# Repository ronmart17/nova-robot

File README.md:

# NOVA — a small desktop robot with a Raspberry Pi 5 brain

NOVA is a palm-sized home robot designed end to end: electronics, PCBs, enclosure, charging dock, simulations and
documentation. A Raspberry Pi 5 does vision, voice and the link to cloud AI models. An ESP32-S3 keeps the body alive:
motors, sensors, display face and power. The robot drives back to a 12 V dock by itself to charge.

> **Status:** Rev B design complete and verified (ERC/DRC clean, mechanical interference check, circuit and system
> simulations). The physical prototype has not been built yet.

| | |
|---|---|
|  |  |
| On its charging dock (AprilTag for the return trip) | Five-part enclosure: white body, graphite skirt, smoked visor, light halo |
|  |  |
| Internals: main board, 2S2P pack, Pi 5, XVF3800 mic array, head board | Rear: speaker grille, USB-C, power switch, dock opening |

## What is inside

| Block | Parts |
|---|---|
| Brain | Raspberry Pi 5 + Active Cooler, Camera Module 3, ReSpeaker XVF3800 4-mic array with echo cancellation |
| Body controller | ESP32-S3-WROOM-1 (N16R8), TCA9535 I/O expander, LSM6DSOX IMU |
| Drive | 2 × N20 gear motors with Hall encoders, TB6612FNG, ball caster |
| Sensors | 2 × VL53L4CD cliff ToF, VL53L1X front ToF, AT42QT1010 capacitive touch |
| Face | 2.0" ST7789 IPS display behind a smoked acrylic visor |
| Power | 2S2P 18650 (44 Wh), R5460 protector, TI BQ25798 buck-boost NVDC charger with two inputs (USB-C and 12 V dock), TPS566238 6 A for the Pi 5, TPS62933 for 3.3 V |
| Dock | 12 V input with PTC, reverse-polarity FET and TVS, spring pogo contacts, AprilTag target |
| Pi ↔ ESP32 | UART0 (the Pi can re-flash the ESP32 through its ROM bootloader), shutdown/reset/boot lines |

Cloud AI: the hardware is laid out so that the Pi 5 runs the voice pipeline (wake word and audio from the XVF3800)
and calls hosted LLM, speech and vision APIs over Wi-Fi, while light models (wake word, AprilTag, small vision models)
run on the device. The firmware and software are the next step.

## Boards (KiCad 10)

| Board | Layers | Size | Verification |
|---|---|---|---|
| `nova-main` | 4 | 136 × 136 mm | ERC 0 (3 documented exclusions), DRC 0, 0 unconnected, schematic parity 0 |
| `nova-head` | 2 | 76 × 74.9 mm | ERC 0, DRC 0, 0 unconnected, parity 0 |
| `nova-dock` | 2 | 58 × 34 mm + break-away contact plate | ERC 0, DRC 0, 0 unconnected, parity 0 |

| | | |
|---|---|---|
|  |  |  |
| Main board | Head board | Dock board |

Each board has JLCPCB-ready Gerbers, BOM and CPL files, a full BOM with Mouser/DigiKey codes, assembly drawings,
a 1:1 mechanical drawing and STEP in `hardware/<board>/fabrication/`.

## Simulations

Circuit simulations in ngspice and system analyses in Python. Full report:
[simulations/NOVA_RevB_simulations.pdf](simulations/NOVA_RevB_simulations.pdf).

| Check | Result |
|---|---|
| Pi 5 rail, 1 → 3 A load step (behavioural D-CAP3 model) | ≥ 4.90 V at the Pi (under-voltage at 4.63 V), 3.9 mV ripple |
| VSYS with both motors under PWM | 46 mV p-p driving, 108 mV p-p with both motors stalled |
| Dock and USB-C hot plug, reverse polarity | ≤ 19.5 V at the charger input (30 V max), reversed adapter blocked |
| I2C and display SPI edges | 207 ns rise time (≤ 300 ns), SPI ringing removed with a lower drive strength |
| Runtime (44 Wh) | 10 h idle, 6.9 h in conversation, 4.3 h at full load, 11 days standby |
| Docking (Monte Carlo) | 99 % first-try success with the recommended approach procedure |
| Stability, thermal, pogo-contact current, battery protection | see the report |

## Repository layout

```
docs/          design document (MD + PDF), images, verification summary
hardware/      KiCad 10 projects: nova-main, nova-head, nova-dock, project library (lib/), fabrication outputs
mechanics/     CadQuery enclosure and assembly (Python), renders, printed parts (STEP + STL), assembly STEP
generator/     Python generators for the schematics, footprints, PCB placement/routing and the documentation
simulations/   ngspice and Python models, netlists, plots, results and the simulation report
```

The schematics and boards are generated by the scripts in `generator/` (including an in-house PathFinder-style
router); the enclosure is parametric CadQuery code driven by `mechanics/dims.py`. The scripts were written for the
author's build environment (KiCad 10.0.7 built from source, absolute paths), so treat them as reference.

## Tools

KiCad 10 · ngspice 42 · CadQuery / OpenCascade · Python (numpy, matplotlib, pyvista)

## Author and licence

Designed by **Caril Ronnie Martínez Vera** — electronics and telecommunications engineer.
© 2026, all rights reserved: see [LICENSE](LICENSE). The files are published for viewing only.

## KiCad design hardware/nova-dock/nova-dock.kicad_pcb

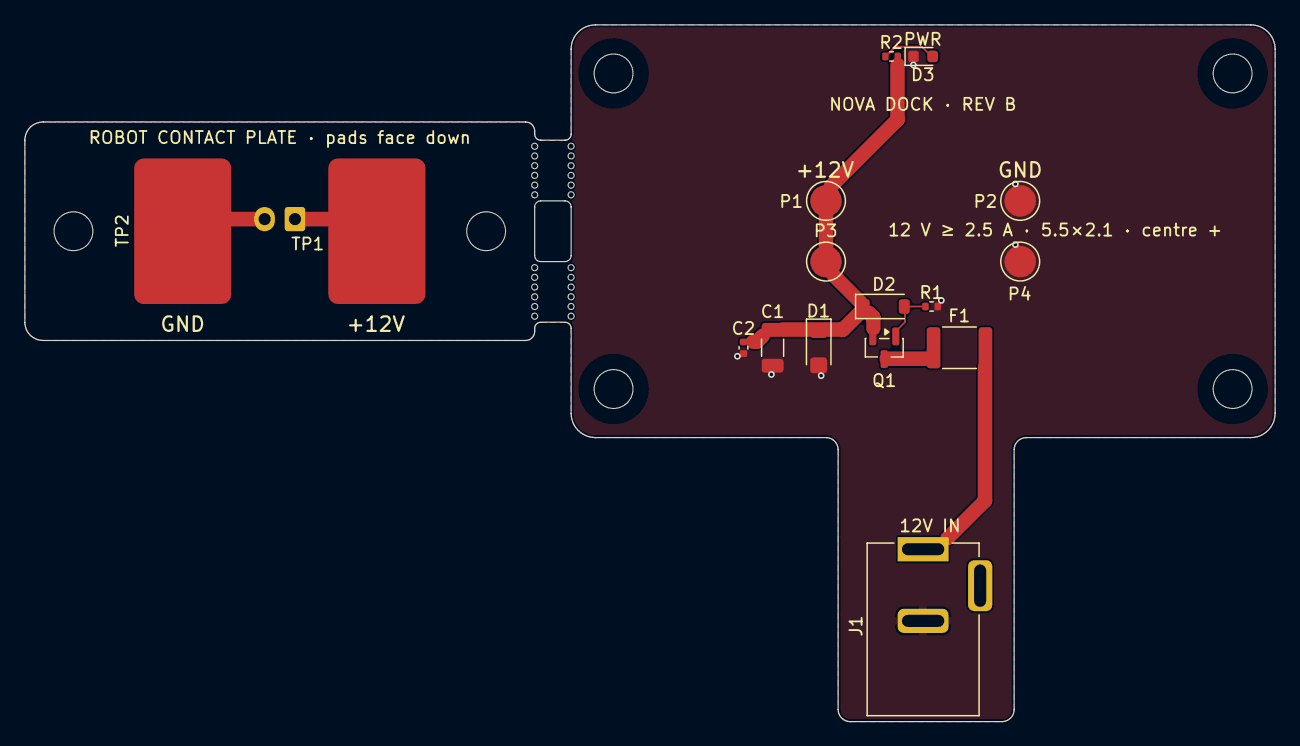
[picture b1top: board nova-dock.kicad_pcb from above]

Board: 2 copper layers, 103.0 x 57.4 mm, 25 parts (1 on the bottom side), 8 nets.

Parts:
C1: 22u/25V; C_1206_3216Metric
C2: 100n; C_0402_1005Metric
D1: SMF15A; D_SMF
D2: BZT52C10; D_SOD-123
D3: Green; LED_0603_1608Metric
F1: 3A hold; Fuse_1812_4532Metric
H1, H2, H3, H4, H5, H6: M3; MountingHole_3.2mm_M3
J1: 12V IN; DC_Jack_XKB_DC-005-5A-2.0_Horizontal
J2: TO ROBOT; JST_XH_B2B-XH-A_1x02_P2.50mm_Vertical
MB1, MB2: TAB; MouseBite_Tab_5x3mm
P1, P2, P3, P4: POGO; Pogo_YTC1P-8020_D2.0mm
Q1: AO3401A; SOT-23
R1: 10k; R_0402_1005Metric
R2: 4.7k; R_0402_1005Metric
TP1, TP2: CONTACT; ContactPad_8x12mm

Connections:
/PLATE_GND: J2.2, TP2.1 (1_1)
/PLATE_POS: J2.1, TP1.1 (1_1)
/VDOCK_OUT: C1.1, C2.1, D1.1 (A1), D2.1 (K), P1.1 (Pin_1_1), P3.1 (Pin_1_1), Q1.2 (S), R2.1
GND: C1.2, C2.2, D1.2 (A2), D3.1 (K), J1.2, P2.1 (Pin_1_1), P4.1 (Pin_1_1), R1.2
unnamed: D2.2 (A), Q1.1 (G), R1.1
unnamed: D3.2 (A), R2.2
unnamed: F1.1, J1.1
unnamed: F1.2, Q1.3 (D)

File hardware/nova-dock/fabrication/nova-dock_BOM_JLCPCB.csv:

Comment,Designator,Footprint,JLCPCB Part #
22u/25V,C1,C_1206_3216Metric,C12891
100n,C2,C_0402_1005Metric,C307331
SMF15A,D1,D_SMF,C123802
BZT52C10,D2,D_SOD-123,C173431
Green,D3,LED_0603_1608Metric,C125098
3A hold,F1,Fuse_1812_4532Metric,C883162
12V IN,J1,DC_Jack_XKB_DC-005-5A-2.0_Horizontal,C381116
TO ROBOT,J2,JST_XH_B2B-XH-A_1x02_P2.50mm_Vertical,C158012
POGO,"P1,P2,P3,P4",Pogo_YTC1P-8020_D2.0mm,C5221286
AO3401A,Q1,SOT-23,C15127
10k,R1,R_0402_1005Metric,C60490
4.7k,R2,R_0402_1005Metric,C105871

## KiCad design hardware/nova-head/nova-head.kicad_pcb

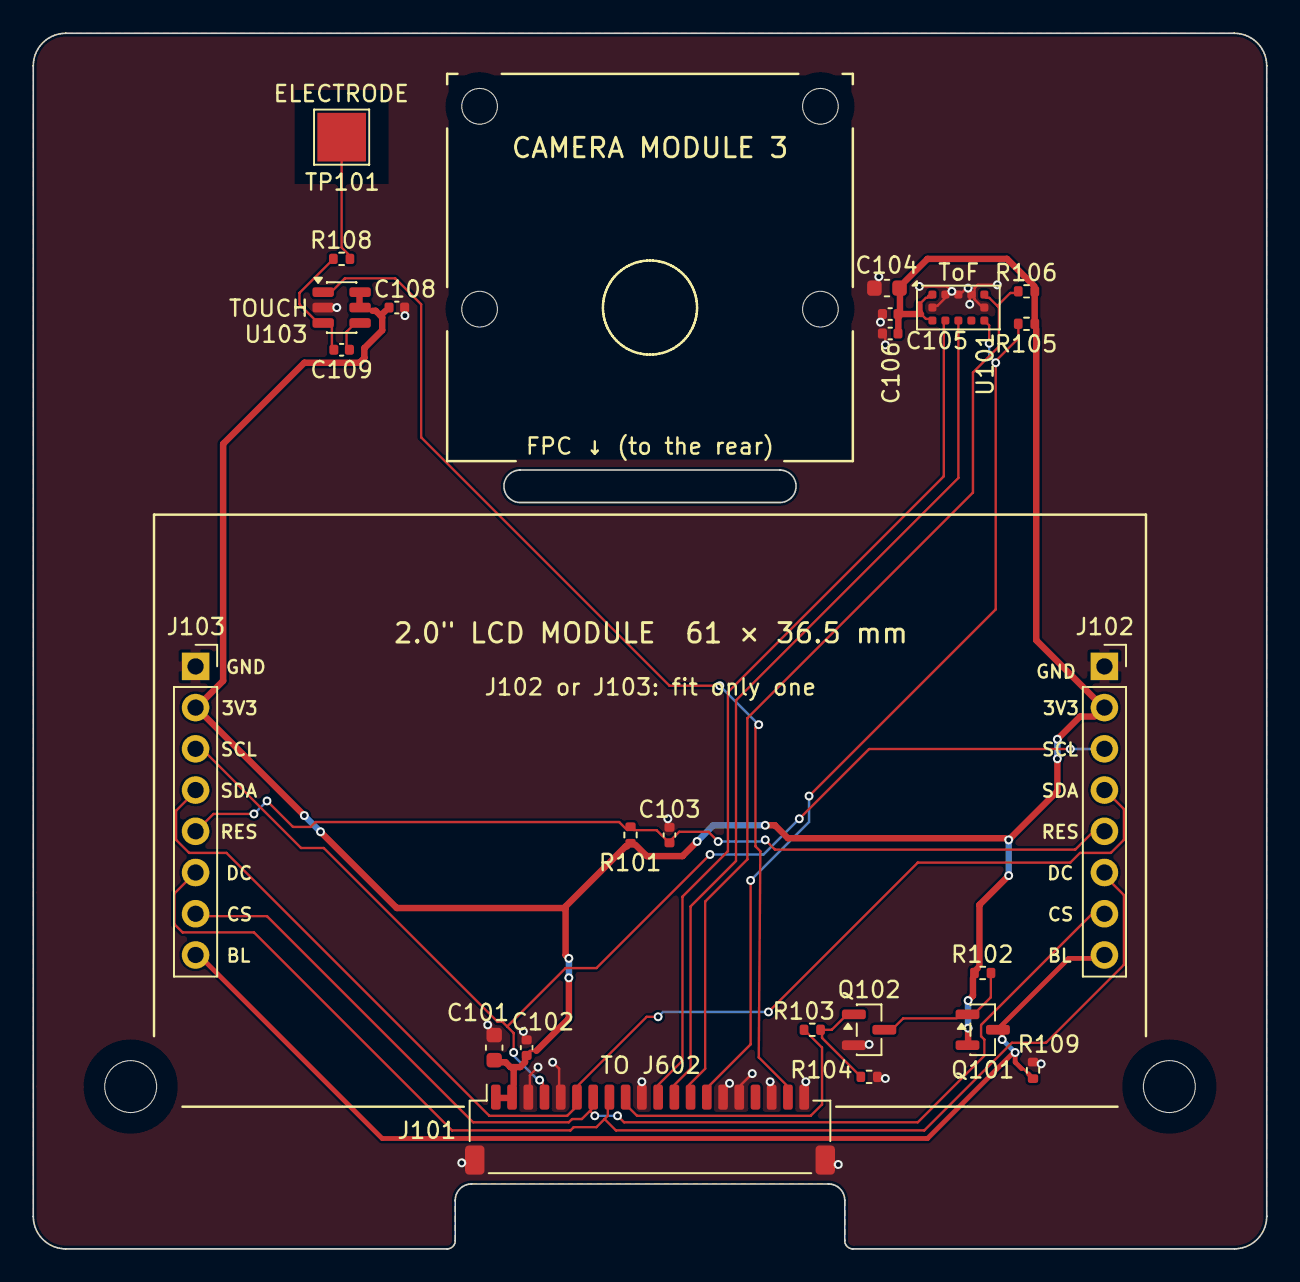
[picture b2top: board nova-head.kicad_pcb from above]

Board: 2 copper layers, 76.0 x 74.9 mm, 30 parts (0 on the bottom side), 19 nets.

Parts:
C101: 10u/10V; C_0603_1608Metric
C102, C103, C105, C106, C108: 100n; C_0402_1005Metric
C104: 4.7u/16V; C_0603_1608Metric
C109: 8.2n; C_0402_1005Metric
H101, H102: M3; MountingHole_3.2mm_M3
H103, H104, H105, H106: M2; MountingHole_2.2mm_M2
J101: HEAD; JST_SH_SM20B-SRSS-TB_1x20-1MP_P1.00mm_Horizontal
J102, J103: LCD ST7789; PinSocket_1x08_P2.54mm_Vertical
Q101: AO3401A; SOT-23
Q102: 2N7002LT1G; SOT-23
R101, R102, R105, R106: 10k; R_0402_1005Metric
R103: 100R; R_0402_1005Metric
R104: 100k; R_0402_1005Metric
R108: 4.7k; R_0402_1005Metric
R109: 1k; R_0402_1005Metric
TP101: TOUCH; TestPoint_Pad_3.0x3.0mm
U101: VL53L1CXV0FY/1; ST_VL53L1x
U103: AT42QT1010-TSHR; SOT-23-6

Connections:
+3V3: C101.1, C102.1, C104.1, C105.1, C106.1, C108.1, J101.1, J101.2, J102.2, J103.2, Q101.2 (S), R101.1, R102.1, R105.1, R106.1, U101.1 (AVDDVCSEL), U101.11 (AVDD), U103.5 (VDD), U103.6 (SYNC)
/BL_OUT: J102.8, J103.8, Q101.3 (D), R109.1
/I2C_SCL: J101.11, U101.10 (SCL)
/I2C_SDA: J101.12, U101.9 (SDA)
/LCD_BL: J101.9, R103.1
/LCD_CS: J101.7, J102.7, J103.7
/LCD_DC: J101.8, J102.6, J103.6
/LCD_MOSI: J101.6, J102.4, J103.4
/LCD_RES: C103.1, J102.5, J103.5, R101.2
/LCD_SCLK: J101.4, J102.3, J103.3
/TOF_INT: J101.14, R105.2, U101.7 (GPIO1)
/TOF_XSHUT: J101.13, R106.2, U101.5 (XSHUT)
/TOUCH: J101.19, U103.1 (OUT)
GND: C101.2, C102.2, C103.2, C104.2, C105.2, C106.2, C108.2, J101.3, J101.5, J101.10, J101.15, J101.16, J101.18, J101.20, J101.MP (MountPin), J102.1, J103.1, Q102.2 (S), R104.2, R109.2, U101.2 (AVSSVCSEL), U101.3 (GND), U101.4 (GND), U101.6 (GND), U101.12 (GND), U103.2 (VSS)
unnamed: Q101.1 (G), Q102.3 (D), R102.2
unnamed: Q102.1 (G), R103.2, R104.1
unnamed: R108.2, TP101.1 (1_1)
unnamed: C109.2, U103.4 (SNS)
unnamed: C109.1, R108.1, U103.3 (SNSK)

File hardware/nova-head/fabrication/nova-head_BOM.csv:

Item,Qty,Designators,Value,Footprint,Manufacturer,MPN,LCSC,Mouser,DigiKey,Alt MPN,Alt Mouser,Alt DigiKey,Description,Sourcing note,DNP
1,1,C101,10u/10V,C_0603_1608Metric,Yageo,CC0603KRX5R6BB106,C326057,603-CC603KRX5R6BB106,,,,,MLCC 10uF 10V X5R 0603,JLC Basic alt C19702,
2,5,"C102, C103, C105, C106, C108",100n,C_0402_1005Metric,Samsung,CL05B104KB54PNC,C307331,187-CL05B104KB54PNC,1276-CL05B104KB54PNCCT-ND,,,,MLCC 100nF 50V X7R 0402,JLC Basic,
3,1,C104,4.7u/16V,C_0603_1608Metric,Samsung,CL10A475KO8NNNC,C19666,,1276-1784-1-ND,,,,MLCC 4.7uF 16V X5R 0603,JLC Basic,
4,1,C109,8.2n,C_0402_1005Metric,Yageo,CC0402KRX7R9BB822,C107032,603-CC402KRX7R9BB822,311-3817-1-ND,,,,MLCC 8.2nF 50V X7R 0402 — QT1010 Cs,,
5,1,J101,HEAD,JST_SH_SM20B-SRSS-TB_1x20-1MP_P1.00mm_Horizontal,JST,SM20B-SRSS-TB(LF)(SN),C160415,306-SM20BSRSSTBLFSN,455-SM20B-SRSS-TBCT-ND,,,,JST SH 20-pin SMD — cable to head board,,
6,1,J102,LCD ST7789,PinSocket_1x08_P2.54mm_Vertical,Amphenol FCI,75915-308LF,C3322318,649-75915-308LF,609-3559-ND,,,,"Female header 1x8 2.54 mm — 2.0"" ST7789 240x320 SPI module (GND VCC SCL SDA RES DC CS BLK)",LCSC 151 pcs.,
7,1,J103,LCD ST7789,PinSocket_1x08_P2.54mm_Vertical,Amphenol FCI,75915-308LF,C3322318,649-75915-308LF,609-3559-ND,,,,"Female header 1x8 2.54 mm — 2.0"" ST7789 240x320 SPI module (GND VCC SCL SDA RES DC CS BLK)",LCSC 151 pcs.,DNP
8,1,Q101,AO3401A,SOT-23,Alpha & Omega,AO3401A,C15127,,785-1001-1-ND,,,,"P-MOSFET -30V -4A, VGS ±12V, 60 mOhm@-4.5V, SOT-23",JLC Basic,
9,1,Q102,2N7002LT1G,SOT-23,onsemi,2N7002LT1G,C16338,863-2N7002LT1G,2N7002LT1GOSCT-ND,,,,N-MOSFET 60V 115mA SOT-23,,
10,4,"R101, R102, R105, R106",10k,R_0402_1005Metric,Yageo,RC0402FR-0710KL,C60490,603-RC0402FR-0710KL,311-10.0KLRCT-ND,,,,Thick-film resistor 10k 1% 0402,,
11,1,R103,100R,R_0402_1005Metric,Yageo,RC0402FR-07100RL,C106232,603-RC0402FR-07100RL,311-100LRCT-ND,,,,Thick-film resistor 100R 1% 0402,JLC Basic alt C25076,
12,1,R104,100k,R_0402_1005Metric,Yageo,RC0402FR-07100KL,C60491,603-RC0402FR-07100KL,311-100KLRCT-ND,,,,Thick-film resistor 100k 1% 0402,JLC Basic alt C25741,
13,1,R108,4.7k,R_0402_1005Metric,Yageo,RC0402FR-074K7L,C105871,603-RC0402FR-074K7L,,,,,Thick-film resistor 4.7k 1% 0402,JLC Basic alt C25900,
14,1,R109,1k,R_0402_1005Metric,Yageo,RC0402FR-071KL,C106235,603-RC0402FR-071KL,311-1.00KLRCT-ND,,,,Thick-film resistor 1k 1% 0402,JLC Basic alt C11702,
15,1,U101,VL53L1CXV0FY/1,ST_VL53L1x,STMicroelectronics,VL53L1CXV0FY/1,C190004,511-VL53L1CXV0FY/1,497-17764-1-ND,,,,"4m distance ranging ToF sensor, Optical LGA12",,
16,1,U103,AT42QT1010-TSHR,SOT-23-6,Microchip,AT42QT1010-TSHR,C74512,556-AT42QT1010-TSHR,AT42QT1010-TSHRCT-ND,,,,"Single-key Touch Sensor, SOT-23-6",,

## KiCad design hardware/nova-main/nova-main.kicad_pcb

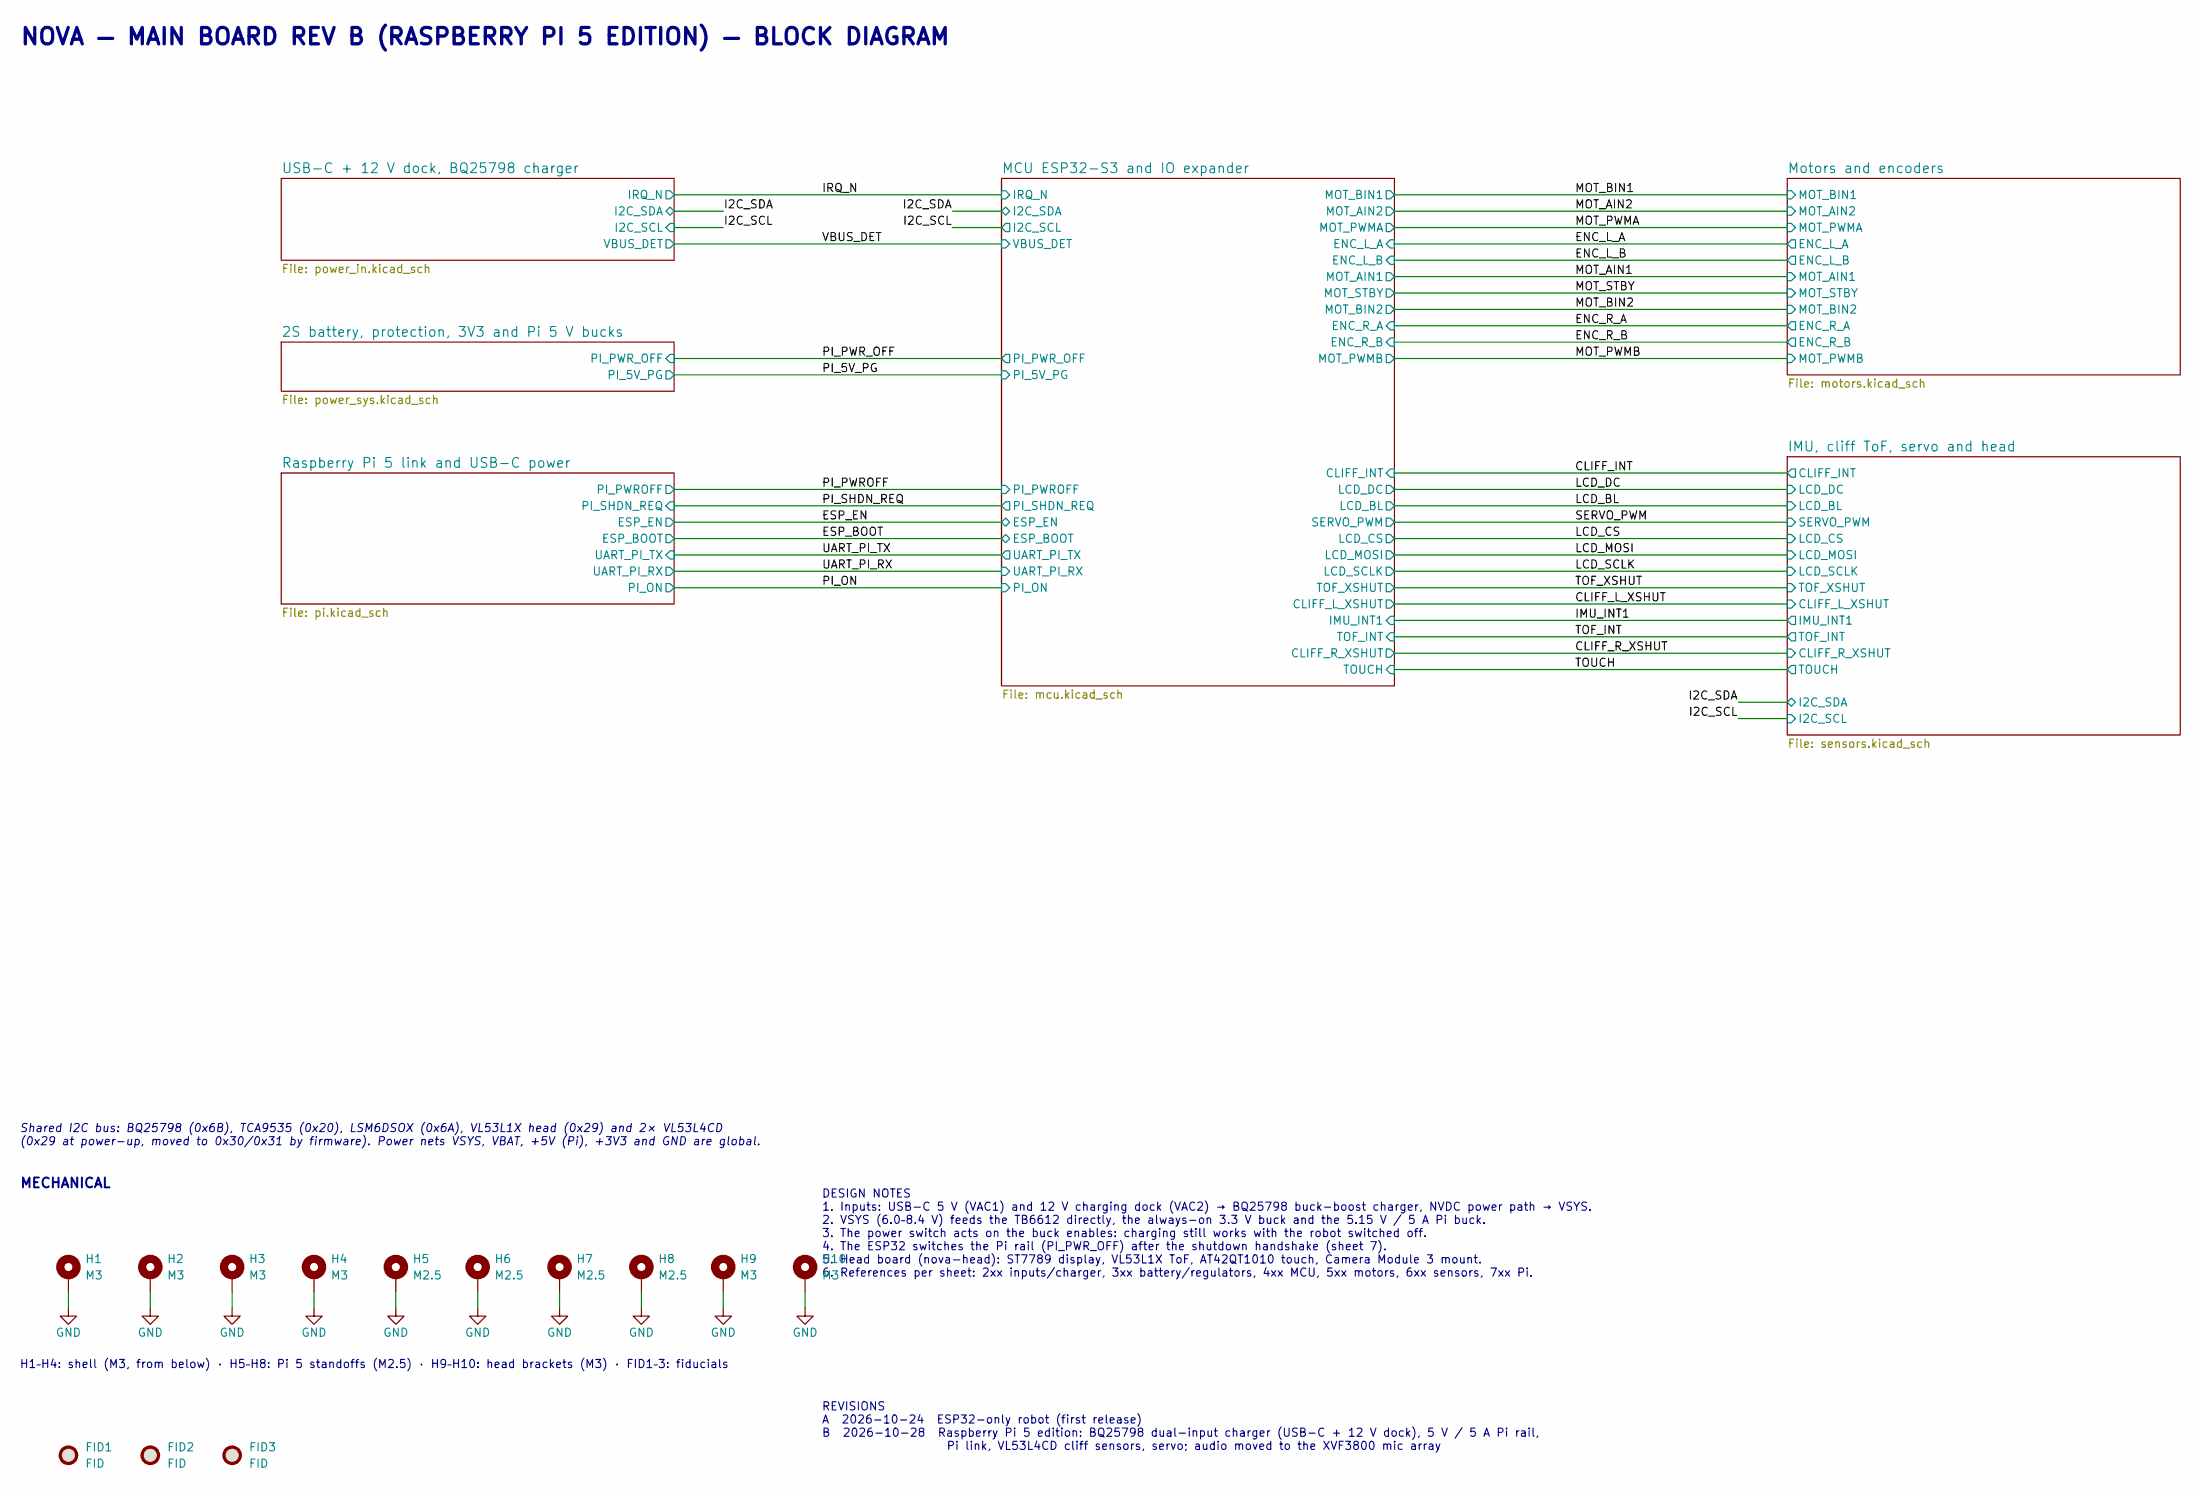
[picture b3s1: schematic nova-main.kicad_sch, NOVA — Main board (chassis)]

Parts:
FID1, FID2, FID3: FID; Fiducial_1mm_Mask2mm
H1, H2, H3, H4, H9, H10: M3; MountingHole_3.2mm_M3_Pad_Via
H5, H6, H7, H8: M2.5; MountingHole_2.7mm_M2.5_Pad_Via

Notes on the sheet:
NOVA — MAIN BOARD REV B (RASPBERRY PI 5 EDITION) — BLOCK DIAGRAM
Shared I2C bus: BQ25798 (0x6B), TCA9535 (0x20), LSM6DSOX (0x6A), VL53L1X head (0x29) and 2× VL53L4CD (0x29 at power-up, moved to 0x30/0x31 by firmware). Power nets VSYS, VBAT, +5V (Pi), +3V3 and GND are global.
MECHANICAL
H1–H4: shell (M3, from below) · H5–H8: Pi 5 standoffs (M2.5) · H9–H10: head brackets (M3) · FID1–3: fiducials
DESIGN NOTES 1. Inputs: USB-C 5 V (VAC1) and 12 V charging dock (VAC2) → BQ25798 buck-boost charger, NVDC power path → VSYS. 2. VSYS (6.0–8.4 V) feeds the TB6612 directly, the always-on 3.3 V buck and the 5.15 V / 5 A Pi buck. 3. The power switch acts on the buck enables: charging still works with 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
REVISIONS A 2026-10-24 ESP32-only robot (first release) B 2026-10-28 Raspberry Pi 5 edition: BQ25798 dual-input charger (USB-C + 12 V dock), 5 V / 5 A Pi rail, Pi link, VL53L4CD cliff sensors, servo; audio moved to the XVF3800 mic array

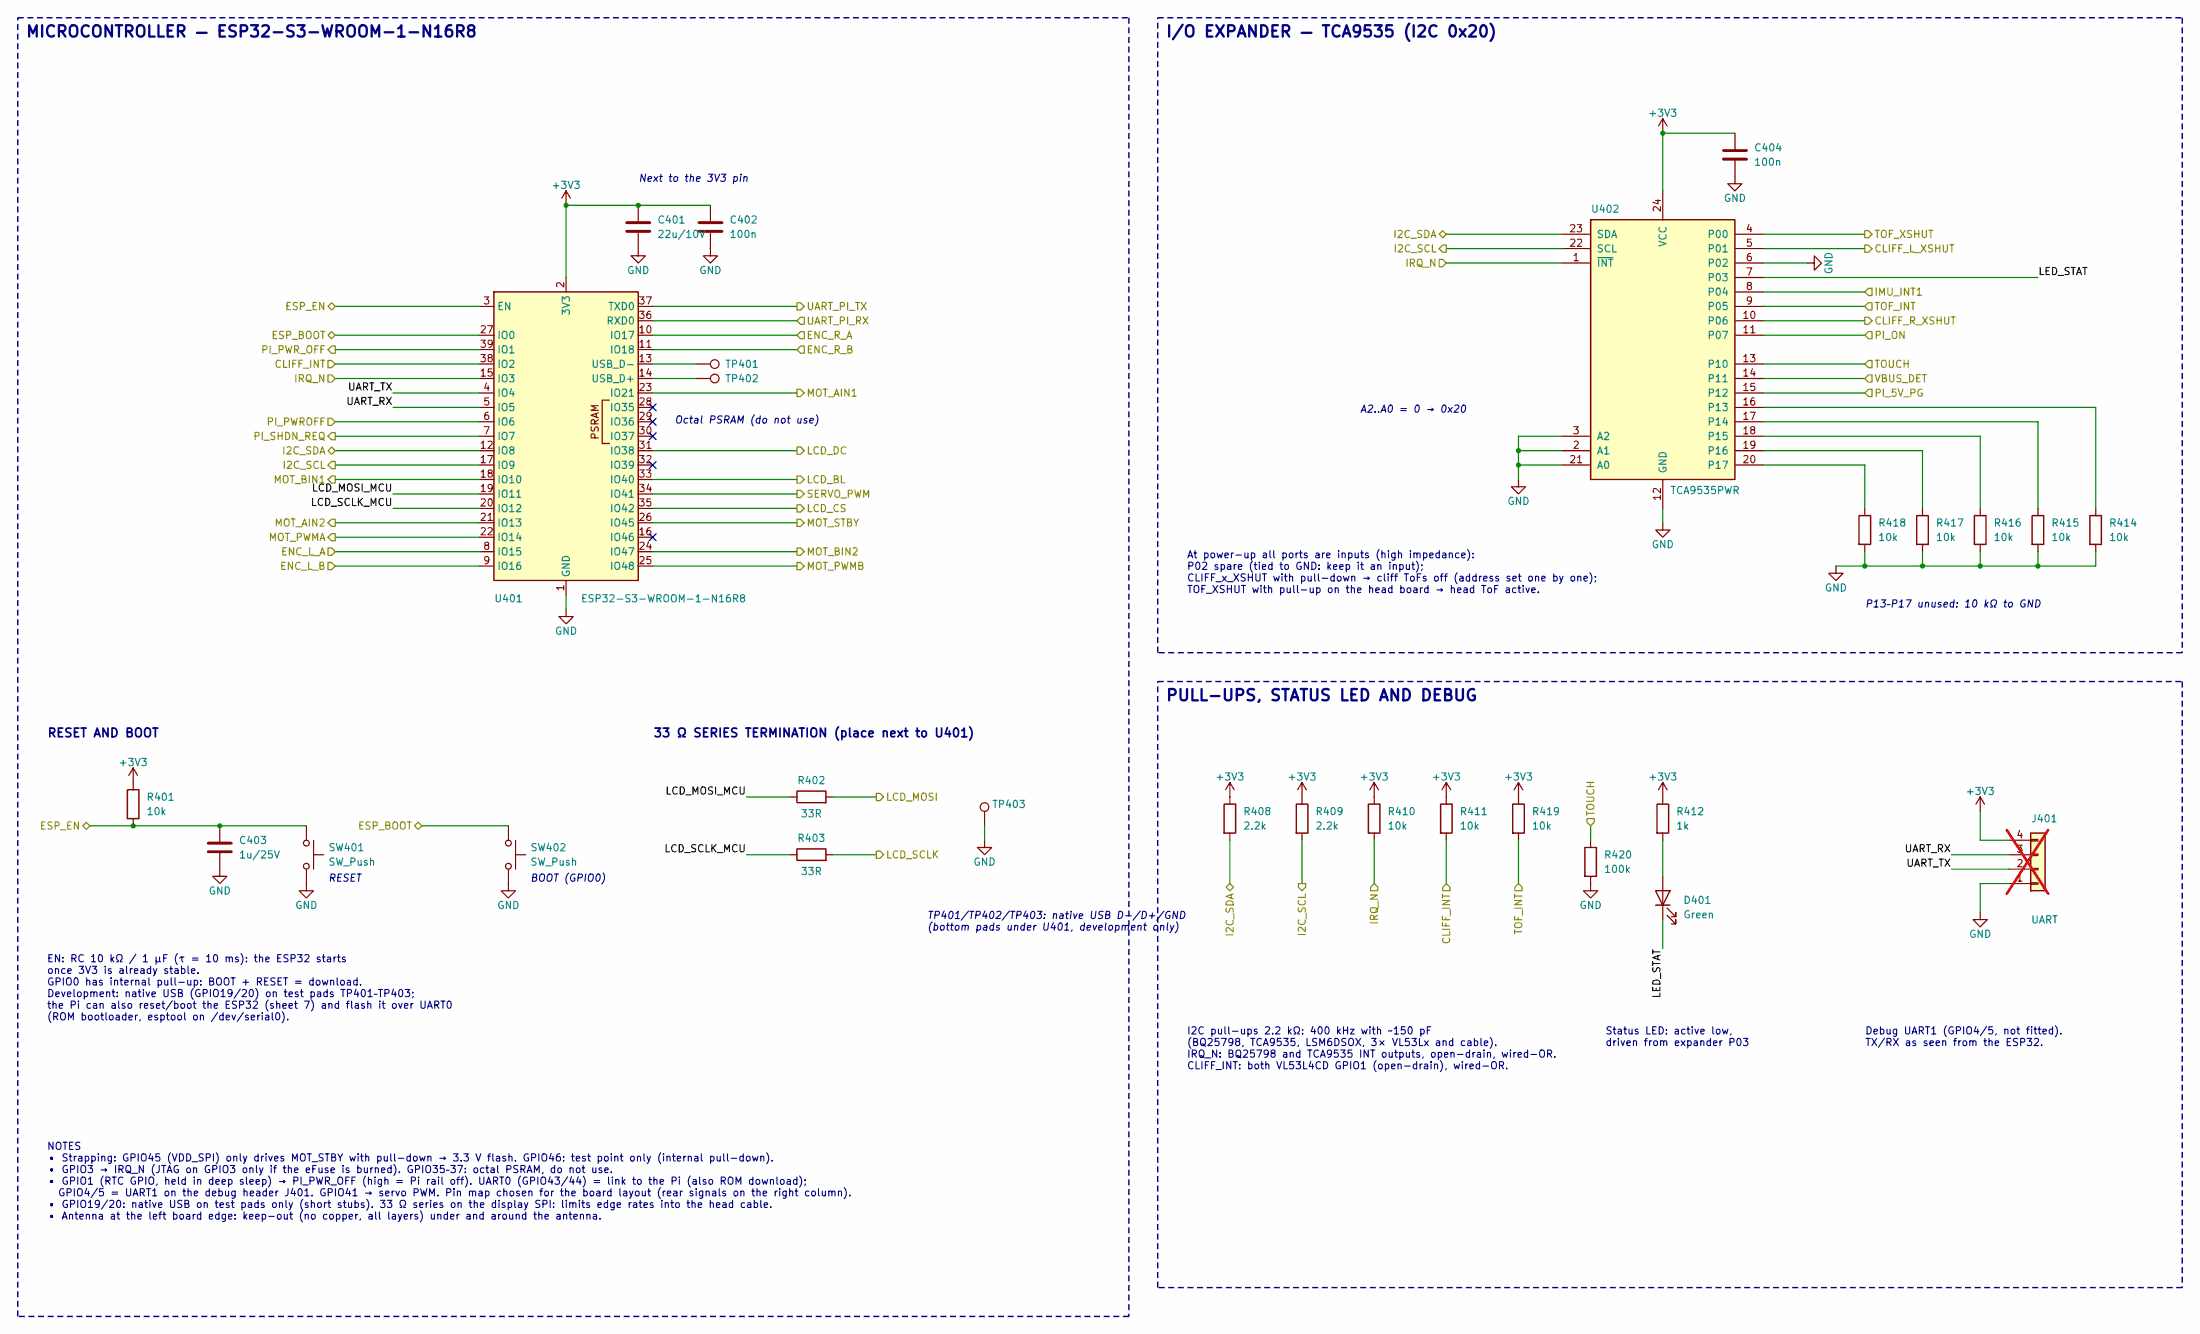
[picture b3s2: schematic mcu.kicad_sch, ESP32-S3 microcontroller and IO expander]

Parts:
C401: 22u/10V; C_0805_2012Metric; Voltage 10V; MPN LMK212BJ226MG-T; LCSC C92814
C402, C404: 100n; C_0402_1005Metric; Voltage 50V; MPN CL05B104KB54PNC; LCSC C307331
C403: 1u/25V; C_0402_1005Metric; Voltage 25V; MPN CL05A105KA5NQNC; LCSC C52923
D401: Green; LED_0603_1608Metric; MPN LTST-C191KGKT; LCSC C125098
J401: UART; PinHeader_1x04_P2.54mm_Vertical; MPN 22-28-4040; LCSC C587039; not fitted
R401, R410, R411, R414, R415, R416, R417, R418, R419: 10k; R_0402_1005Metric; Tolerance 1%; MPN RC0402FR-0710KL; LCSC C60490
R402, R403: 33R; R_0402_1005Metric; Tolerance 1%; MPN RC0402FR-0733RL; LCSC C138002
R408, R409: 2.2k; R_0402_1005Metric; Tolerance 1%; MPN RC0402FR-072K2L; LCSC C114762
R412: 1k; R_0402_1005Metric; Tolerance 1%; MPN RC0402FR-071KL; LCSC C106235
R420: 100k; R_0402_1005Metric; Tolerance 1%; MPN RC0402FR-07100KL; LCSC C60491
SW401, SW402: SW_Push; SW_SPST_PTS810; MPN PTS810SJK250SMTRLFS; LCSC C221896
TP401, TP402, TP403: TP; TestPoint_Pad_D1.5mm
U401: ESP32-S3-WROOM-1-N16R8; ESP32-S3-WROOM-1; MPN ESP32-S3-WROOM-1-N16R8; LCSC C2913202
U402: TCA9535PWR; TSSOP-24_4.4x7.8mm_P0.65mm; MPN TCA9535PWR; LCSC C130204

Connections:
/CLIFF_INT: R411.2, U401.38 (IO2); also elsewhere on the board
/CLIFF_L_XSHUT: U402.5 (P01); also elsewhere on the board
/CLIFF_R_XSHUT: U402.10 (P06); also elsewhere on the board
/ENC_L_A: U401.8 (IO15); also elsewhere on the board
/ENC_L_B: U401.9 (IO16); also elsewhere on the board
/ENC_R_A: U401.10 (IO17); also elsewhere on the board
/ENC_R_B: U401.11 (IO18); also elsewhere on the board
/ESP_BOOT: SW402.1, U401.27 (IO0); also elsewhere on the board
/ESP_EN: C403.1, R401.2, SW401.1, U401.3 (EN); also elsewhere on the board
/I2C_SCL: R409.2, U401.17 (IO9), U402.22 (SCL); also elsewhere on the board
/I2C_SDA: R408.2, U401.12 (IO8), U402.23 (SDA); also elsewhere on the board
/IMU_INT1: U402.8 (P04); also elsewhere on the board
/IRQ_N: R410.2, U401.15 (IO3), U402.1 (~INT); also elsewhere on the board
/LCD_BL: U401.33 (IO40); also elsewhere on the board
/LCD_CS: U401.35 (IO42); also elsewhere on the board
/LCD_DC: U401.31 (IO38); also elsewhere on the board
/LCD_MOSI: R402.2; also elsewhere on the board
/LCD_SCLK: R403.2; also elsewhere on the board
/MCU ESP32-S3 and IO expander/LCD_MOSI_MCU: R402.1, U401.19 (IO11)
/MCU ESP32-S3 and IO expander/LCD_SCLK_MCU: R403.1, U401.20 (IO12)
/MCU ESP32-S3 and IO expander/LED_STAT: D401.1 (K), U402.7 (P03)
/MCU ESP32-S3 and IO expander/UART_RX: J401.3, U401.5 (IO5)
/MCU ESP32-S3 and IO expander/UART_TX: J401.2, U401.4 (IO4)
/MOT_AIN1: U401.23 (IO21); also elsewhere on the board
/MOT_AIN2: U401.21 (IO13); also elsewhere on the board
/MOT_BIN1: U401.18 (IO10); also elsewhere on the board
/MOT_BIN2: U401.24 (IO47); also elsewhere on the board
/MOT_PWMA: U401.22 (IO14); also elsewhere on the board
/MOT_PWMB: U401.25 (IO48); also elsewhere on the board
/MOT_STBY: U401.26 (IO45); also elsewhere on the board
/PI_5V_PG: U402.15 (P12); also elsewhere on the board
/PI_ON: U402.11 (P07); also elsewhere on the board
/PI_PWROFF: U401.6 (IO6); also elsewhere on the board
/PI_PWR_OFF: U401.39 (IO1); also elsewhere on the board
/PI_SHDN_REQ: U401.7 (IO7); also elsewhere on the board
/SERVO_PWM: U401.34 (IO41); also elsewhere on the board
/TOF_INT: R419.2, U402.9 (P05); also elsewhere on the board
/TOF_XSHUT: U402.4 (P00); also elsewhere on the board
/TOUCH: R420.1, U402.13 (P10); also elsewhere on the board
/UART_PI_RX: U401.36 (RXD0); also elsewhere on the board
/UART_PI_TX: U401.37 (TXD0); also elsewhere on the board
/VBUS_DET: U402.14 (P11); also elsewhere on the board
unnamed: D401.2 (A), R412.2
unnamed: TP402.1 (1_1), U401.14 (USB_D+)
unnamed: TP401.1 (1_1), U401.13 (USB_D-)
unnamed: R414.1, U402.16 (P13)
unnamed: R415.1, U402.17 (P14)
unnamed: R416.1, U402.18 (P15)
unnamed: R417.1, U402.19 (P16)
unnamed: R418.1, U402.20 (P17)

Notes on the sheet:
MICROCONTROLLER — ESP32-S3-WROOM-1-N16R8
I/O EXPANDER — TCA9535 (I2C 0x20)
PULL-UPS, STATUS LED AND DEBUG
Octal PSRAM (do not use)
TP401/TP402/TP403: native USB D−/D+/GND (bottom pads under U401, development only)
Next to the 3V3 pin
RESET AND BOOT
RESET
BOOT (GPIO0)
EN: RC 10 kΩ / 1 µF (τ = 10 ms): the ESP32 starts once 3V3 is already stable. GPIO0 has internal pull-up: BOOT + RESET = download. Development: native USB (GPIO19/20) on test pads TP401–TP403; the Pi can also reset/boot the ESP32 (sheet 7) and flash it over UART0 (ROM bootloader, esptool on /dev/se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
33 Ω SERIES TERMINATION (place next to U401)
NOTES • Strapping: GPIO45 (VDD_SPI) only drives MOT_STBY with pull-down → 3.3 V flash. GPIO46: test point only (internal pull-down). • GPIO3 → IRQ_N (JTAG on GPIO3 only if the eFuse is burned). GPIO35–37: octal PSRAM, do not use. • GPIO1 (RTC GPIO, held in deep sleep) → PI_PWR_OFF (high = Pi rail o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
A2..A0 = 0 → 0x20
P13–P17 unused: 10 kΩ to GND
At power-up all ports are inputs (high impedance): P02 spare (tied to GND: keep it an input); CLIFF_x_XSHUT with pull-down → cliff ToFs off (address set one by one); TOF_XSHUT with pull-up on the head board → head ToF active.
I2C pull-ups 2.2 kΩ: 400 kHz with ~150 pF (BQ25798, TCA9535, LSM6DSOX, 3× VL53Lx and cable). IRQ_N: BQ25798 and TCA9535 INT outputs, open-drain, wired-OR. CLIFF_INT: both VL53L4CD GPIO1 (open-drain), wired-OR.
Status LED: active low, driven from expander P03
Debug UART1 (GPIO4/5, not fitted). TX/RX as seen from the ESP32.
